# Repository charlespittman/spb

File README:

SecureBox - Locking mailbox based around a Raspberry Pi.

====================
GPIO Pins (BCM numbers)
====================
Door:
lock = 20
unlock = 21
door switch = 5
mail trigger= 16

GSM:
UART pins

RFID:
CS = 18
MOSI = 23
MISO = 24
SCLK = 25

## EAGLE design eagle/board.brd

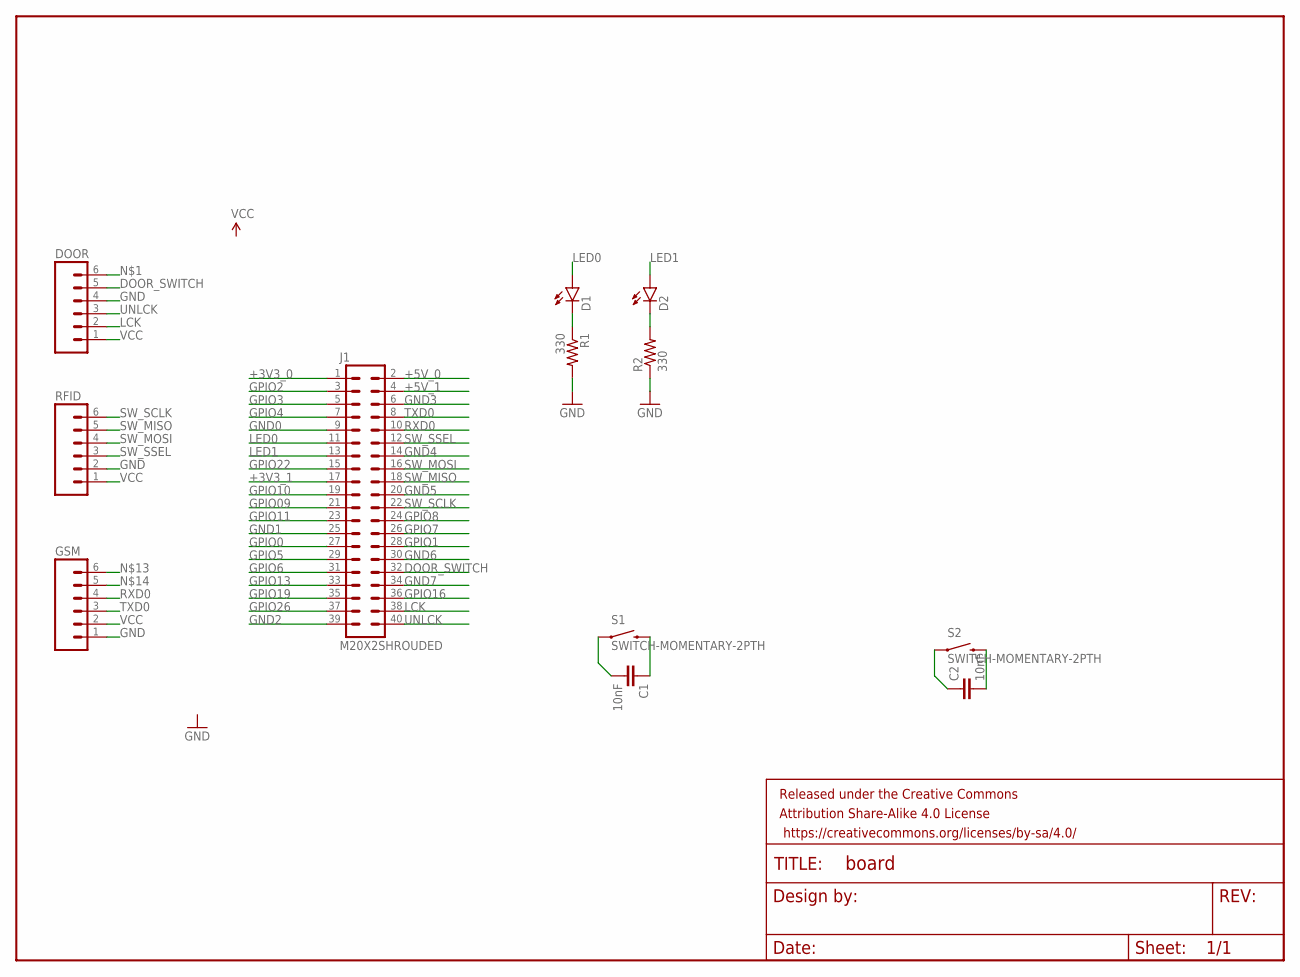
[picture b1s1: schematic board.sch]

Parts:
C1, C2: 10nF; CAP-PTH-SMALL
D1, D2: LED5MM
DOOR: M06LOCK; 1X06_LOCK
FRAME1: FRAME-LETTER; CREATIVE_COMMONS
GSM: M06LOCK; 1X06_LOCK
J1: M20X2SHROUDED; 2X20_SHROUDED
R1, R2: 330; AXIAL-0.4
RFID: M06LOCK; 1X06_LOCK
S1, S2: SWITCH-MOMENTARY-2PTH; TACTILE-PTH

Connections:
+3V3_0: J1.1
+3V3_1: J1.17
+5V_0: J1.2
+5V_1: J1.4
DOOR_SWITCH: DOOR.5, J1.32
GND: DOOR.4, GSM.1, R1.P$2 (2), R2.P$1 (1), RFID.2
GND0: J1.9
GND1: J1.25
GND2: J1.39
GND3: J1.6
GND4: J1.14
GND5: J1.20
GND6: J1.30
GND7: J1.34
GPIO1: J1.28
GPIO2: J1.3
GPIO3: J1.5
GPIO4: J1.7
GPIO5: J1.29
GPIO6: J1.31
GPIO7: J1.26
GPIO8: J1.24
GPIO09: J1.21
GPIO10: J1.19
GPIO11: J1.23
GPIO13: J1.33
GPIO16: J1.36
GPIO19: J1.35
GPIO22: J1.15
GPIO26: J1.37
LCK: DOOR.2, J1.38
LED0: D1.A, J1.11
LED1: D2.A, J1.13
unnamed: D1.K (C), R1.P$1 (1)
unnamed: D2.K (C), R2.P$2 (2)
unnamed: C1.2, S1.1
unnamed: C1.1, S1.3 (2)
unnamed: C2.1, S2.1
unnamed: C2.2, S2.3 (2)
RXD0: GSM.4, J1.10
SW_MISO: J1.18, RFID.5
SW_MOSI: J1.16, RFID.4
SW_SCLK: J1.22, RFID.6
SW_SSEL: J1.12, RFID.3
TXD0: GSM.3, J1.8
UNLCK: DOOR.3, J1.40
VCC: DOOR.1, GSM.2, RFID.1

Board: 2 copper layers, 13 parts (0 on the bottom side), 19 nets, no tracks yet.

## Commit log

2016-02-11 Adding main file skeleton
2016-02-11 Moving existing scripts to samples directory
2016-02-11 ok here
    nope fish
2016-02-11 ok change
2016-02-16 Adding pins for lock
2016-02-16 Adding some documentation to samples.
2016-02-16 Removing chris's junk
2016-02-16 Added Trigger lock to Relay K2 and Unlock to Relay K1
2016-02-16 Planned ".py" file names and added files for lock/unlock and updated the README
2016-02-16 README updates, added comments to main.py
2016-02-16 Assigned mail switch to PIN 36 and door switch to PIN 37
2016-02-16 Added cam.py code, created documentation folder and subroutine plans to view without Visio
2016-02-16 Updated door_open.py and mail_switch.py with status pins
2016-02-16 Added install notes for pycam
2016-02-16 Sub Routine Plans updated
2016-02-16 Organized README, included calls in other subroutines
    I don't know how to correctly call the other modules so I will
    definitely need some help with that intrusion_check.py is just a place
    holder, the code in it is completely wrong
2016-02-17 Added Main to Subroutine plans
    probably should rename to file too. ehh
2016-02-17 Fixup cam.py
    - Added short description and note about picamera package
    - Removed unrelated stuff (leftovers from copy+paste)
    - Corrected README listing
2016-02-17 README Cleanup
2016-02-17 Fixup door_open.py
    - Removed extraneous comments
    - Removed unused sys import
    - Removed pointless sleep
    - Fixed syntax error(s)
2016-02-17 Empty intrusion_check.py
2016-02-17 Collapse door stuff.
    - Combined lock/unlock
    - Updated README
2016-02-18 Relays are active-low
2016-02-18 Used wrong pin numbering
2016-02-22 Fixup mail_switch.
    - Removed some extra comments.
    - Added a main section.
    - Added is_mail().
2016-02-23 Fixup mail_switch.
    - Removed some extra comments.
    - Added a main section.
    - Added is_mail().
    - Removed extra pin.
2016-02-23 Testing door script
2016-02-23 Added sleep to tests
2016-02-23 Adding prints
2016-02-23 Adding *.pyc to .gitignore
2016-02-24 Removing extra sleeps
2016-02-25 Moved GPIO.cleanup to main
2016-02-25 Modularize door.py
    - Added docstring to lock_door and unlock_door.
    - Updated main.py to import door.py
    - Updated pins in README.
2016-02-25 Adding door switch.
    - Added two functions to read reed switch.
    - Updated README with correct pin.
2016-02-25 Had logic reversed
2016-02-25 fixing is_open
2016-03-02 Simplifying is_open and is_closed
2016-03-02 Testing switch
2016-03-02 Cleaning up mail_switch.py
    - Rename MAILSWITCH to mail_switch
    - Simplified is_mail()
    - Replaced main loop with wait_for_edge()
    - Moved LED stuff to send_mail() so it's in one place. One side-effect
    is that the action is only triggered once.
2016-03-03 Adding gsm.py to hold GSM class
2016-03-03 Adding Door class
2016-03-03 Removing cruft
2016-03-03 Adding helper function to read a line from GSM
2016-03-03 Adding begin() to GSM to keep init() only declarations
2016-03-03 Use more descriptive name when instantiating GSM
2016-03-03 Fixup comment alignment
2016-03-04 Don't need to worry about getting data from the module for now.
2016-03-04 readline should return the line it read
2016-03-08 Used wrong method name
2016-03-08 Add asserts to door class
    lock() and unlock() should fail if door is open.
2016-03-08 Used wrong variable name in is_opened and is_closed
2016-03-08 asserts should have been checking that door is closed
2016-03-08 Updating comments
2016-03-08 Filled in information about programs for README
2016-03-09 Updated logic and programs
2016-03-09 Adding Eagle files
2016-03-09 Adding eagle backups to gitignore
2016-03-09 Adding rest of IO labels to board
2016-03-09 Renaming gnd/pwr signals so they don't route together
2016-03-09 Adding headers for modules
2016-03-09 Adding names to door instantiation
2016-03-09 Adding labels to header nets
2016-03-10 Add cap to switches for debounce
2016-03-10 Rename nets on ribbon connector
2016-03-10 Connect door header
2016-03-10 Connect rfid header
2016-03-10 Connect gsm header
2016-03-10 Rename nets to match signal
2016-03-10 Connect LEDs
2016-03-14 Adding function to get result from a command
2016-03-14 Want to readlines after setting gsm up
2016-03-14 Shorten timeout when running gsm as main
2016-03-14 Adding DEBUG var
2016-03-14 Changing main to run check_test
2016-03-14 Adding docs to get/set in gsm
2016-03-14 Updating defualt timeout
2016-03-21 Some README stuff
2016-03-21 Adding main functions
2016-03-21 Correct comments in door
2016-03-22 Copying readmifare.py to a new file.
2016-03-22 updated Main
2016-04-09 updating docstring
2016-04-09 Set up objects to use.
    - Added door, gsm, rfid
2016-04-09 Combine the sending functions
2016-04-09 Shorten sleep time for locks
2016-04-09 Updates to camera stuff
    - Add main()
    - Pictures now have timestamps
    - Takes 5 picture
2016-04-09 Fix name of reed switch in class
    - Was door_switch, but renamed to switch_pin (forgot to change it earlier).
2016-04-09 Add flag to keep track of lock
2016-04-09 Set scripts executable
    - Set +x
    - Added magic line to each one
2016-04-09 Lock door when main starts.
2016-04-12 Adding print statements to check door status
2016-04-12 Remove initialize() so we don't have to juggle objects around
2016-04-12 Fixing imports
2016-04-12 Fixing serial device
2016-04-19 Adding interrupts for mail alert
2016-04-19 Rename modules to prevent collisions
2016-04-19 Adding mail sensor to Door
2016-04-19 Adding interrupt for mail switch
2016-04-20 Move DEBUG out of toplevel
2016-04-20 Correct pin name
2016-04-20 Change main to function
2016-04-20 Add unlocked attribute
2016-04-20 Fix mail callback
2016-04-20 Adding interrupt for door switch
2016-04-20 Adding interrupt for lock toggle
2016-04-20 Messed up if statement
2016-04-20 Messed up wrong if statement
2016-04-20 Door should only trigger on falling edge
2016-04-20 Rename alert_mail_cb
2016-04-20 Adding docstrings
2016-04-20 Adding debug statements
2016-04-20 Alert if broken into
2016-04-20 Lock door after it closes
2016-04-20 Making docstrings more descriptive
2016-04-20 Grouping constants
2016-04-20 Adding a couple comments
2016-04-20 Add rfid stuff to main loop.
2016-04-20 Move debug statements to door module
2016-04-21 event_detector for door switch should trigger on both edges
2016-04-21 Door was locking too early
2016-04-23 Testing changes
2016-04-23 Revert "Testing changes"
    This reverts commit 403a55861e2126940a149b12232cebb156330957.
2016-04-24 Moving door switch to GPIO5.
    Burnt out GPIO12
2016-04-24 Clean up if can't create objects
2016-04-25 Remove unused files
2016-04-25 un/mount thumbstick
2016-04-25 spb_door.py lost execute bit
2016-04-25 Have GSM send me text
2016-04-25 script did not use gpio
2016-04-25 should have been except clause
2016-04-25 Using different usb port
2016-04-25 Remove debug stuff, and print everything

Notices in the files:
parts and their libraries:
SparkFun-Connectors: Licensing: Creative Commons ShareAlike 4.0 International - https://creativecommons.org/licenses/by-sa/4.0
SparkFun-Aesthetics: Released under the Creative Commons Attribution Share-Alike 4.0 License
SparkFun-Aesthetics: https://creativecommons.org/licenses/by-sa/4.0
